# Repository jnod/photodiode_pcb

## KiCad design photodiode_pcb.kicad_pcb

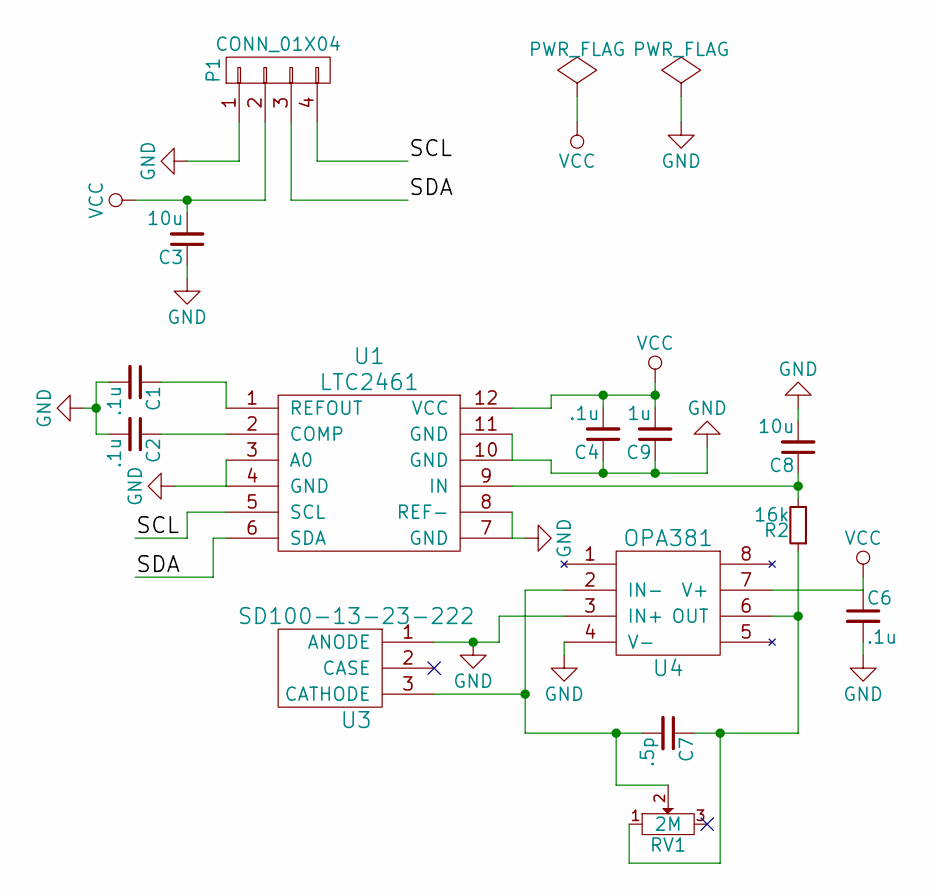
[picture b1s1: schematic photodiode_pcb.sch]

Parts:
C1, C2, C4, C6: .1u; C_0603
C3, C8: 10u; C_0603
C7: .5p; C_0603
C9: 1u; C_0603
P1: CONN_01X04; Sullins_M89_1X4
R2: 16k; R_0603
RV1: 2M; BOURNS_3214W
U1: LTC2461; MSOP-12_3x4mm_Pitch0.65mm
U3: SD100-13-23-222; TO-5-3
U4: OPA381; MSOP-8_3x3mm_Pitch0.65mm

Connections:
/SCL: P1.4, U1.5 (SCL)
/SDA: P1.3, U1.6 (SDA)
GND: C1.2, C2.2, C3.1, C4.1, C6.2, C8.2, C9.1, P1.1, U1.3 (A0), U1.4 (GND), U1.7 (GND), U1.8 (REF-), U1.10 (GND), U1.11 (GND), U3.1 (ANODE), U4.3 (IN+), U4.4 (V-); also elsewhere on the board
unnamed: C1.1, U1.1 (REFOUT)
unnamed: C2.1, U1.2 (COMP)
unnamed: C7.1, R2.1, RV1.1, U4.6 (OUT)
unnamed 6: C7.2, RV1.2, U3.3 (CATHODE), U4.2 (IN-); also elsewhere on the board
unnamed: C8.1, R2.2, U1.9 (IN)
VCC: C3.2, C4.2, C6.1, C9.2, P1.2, U1.12 (VCC), U4.7 (V+)

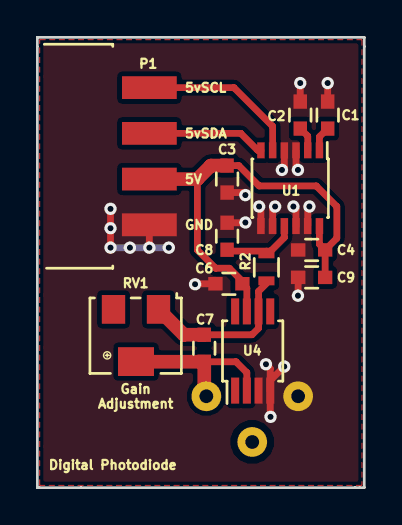
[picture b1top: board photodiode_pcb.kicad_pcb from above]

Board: 2 copper layers, 18.2 x 25.0 mm, 14 parts (1 on the bottom side), 9 nets.

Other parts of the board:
D1: photodiode_asc; TO-5-3

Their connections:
GND: D1.1; also elsewhere on the board
unnamed 6: D1.3; also elsewhere on the board

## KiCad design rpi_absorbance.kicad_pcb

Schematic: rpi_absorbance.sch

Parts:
C1, C2, C4, C5, C6: .1u; C_0603
C3, C9: 1u; C_0603
C7: .5p; C_0603
C8: 10u; C_0603
P1: CONN_01X04; Pin_Header_Straight_1x04
R1: 10M; R_0603
R2: 16k; R_0603
R3, R4: 5k; R_0603
U1: LTC2461; MSOP-12_3x4mm_Pitch0.65mm
U3: SD100-13-23-222; TO-5
U4: OPA381; MSOP-8_3x3mm_Pitch0.65mm

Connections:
/SCL: P1.4, R3.2, U1.5 (SCL)
/SDA: P1.3, R4.1, U1.6 (SDA)
GND: C1.2, C2.2, C3.1, C4.1, C5.1, C6.2, C8.2, C9.1, P1.1, U1.3 (A0), U1.4 (GND), U1.7 (GND), U1.8 (REF-), U1.10 (GND), U1.11 (GND), U3.1 (ANODE), U4.3 (IN+), U4.4 (V-)
unnamed: C1.1, U1.1 (REFOUT)
unnamed: C2.1, U1.2 (COMP)
unnamed: C7.1, R1.1, R2.1, U4.6 (OUT)
unnamed: C7.2, R1.2, U3.3 (CATHODE), U4.2 (IN-)
unnamed: C8.1, R2.2, U1.9 (IN)
VCC: C3.2, C4.2, C5.2, C6.1, C9.2, P1.2, R3.1, R4.2, U1.12 (VCC), U4.7 (V+)

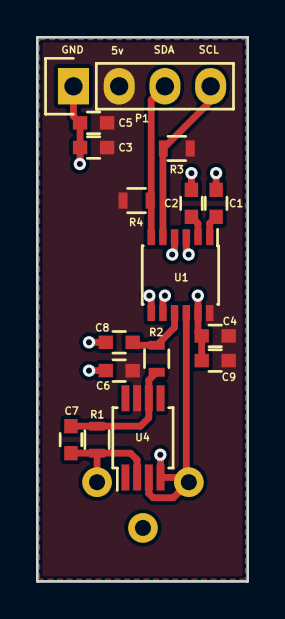
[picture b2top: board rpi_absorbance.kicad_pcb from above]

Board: 2 copper layers, 11.7 x 30.2 mm, 17 parts (1 on the bottom side), 9 nets.

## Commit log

2016-01-17 Add PCB files
2016-01-17 Improve PCB layout
2016-01-17 Add different ADC
2016-01-18 Rearrange components
2016-01-18 Update project
2016-01-20 Reorganize PCB
2016-01-21 Add USB AB micro connector
2016-01-25 Add power planes
2016-01-25 Make final adjustments
2016-01-31 Add I2C resistors and reorganize PCB
2016-02-10 Change footprints
2016-02-22 Renamed files
2016-03-03 Reorganize pcb and change footprints
2016-03-03 Reorganize project
2016-03-03 Update footprints
2016-03-04 Update silk screen
2016-03-06 Update footprint
2016-03-06 Update pcb
